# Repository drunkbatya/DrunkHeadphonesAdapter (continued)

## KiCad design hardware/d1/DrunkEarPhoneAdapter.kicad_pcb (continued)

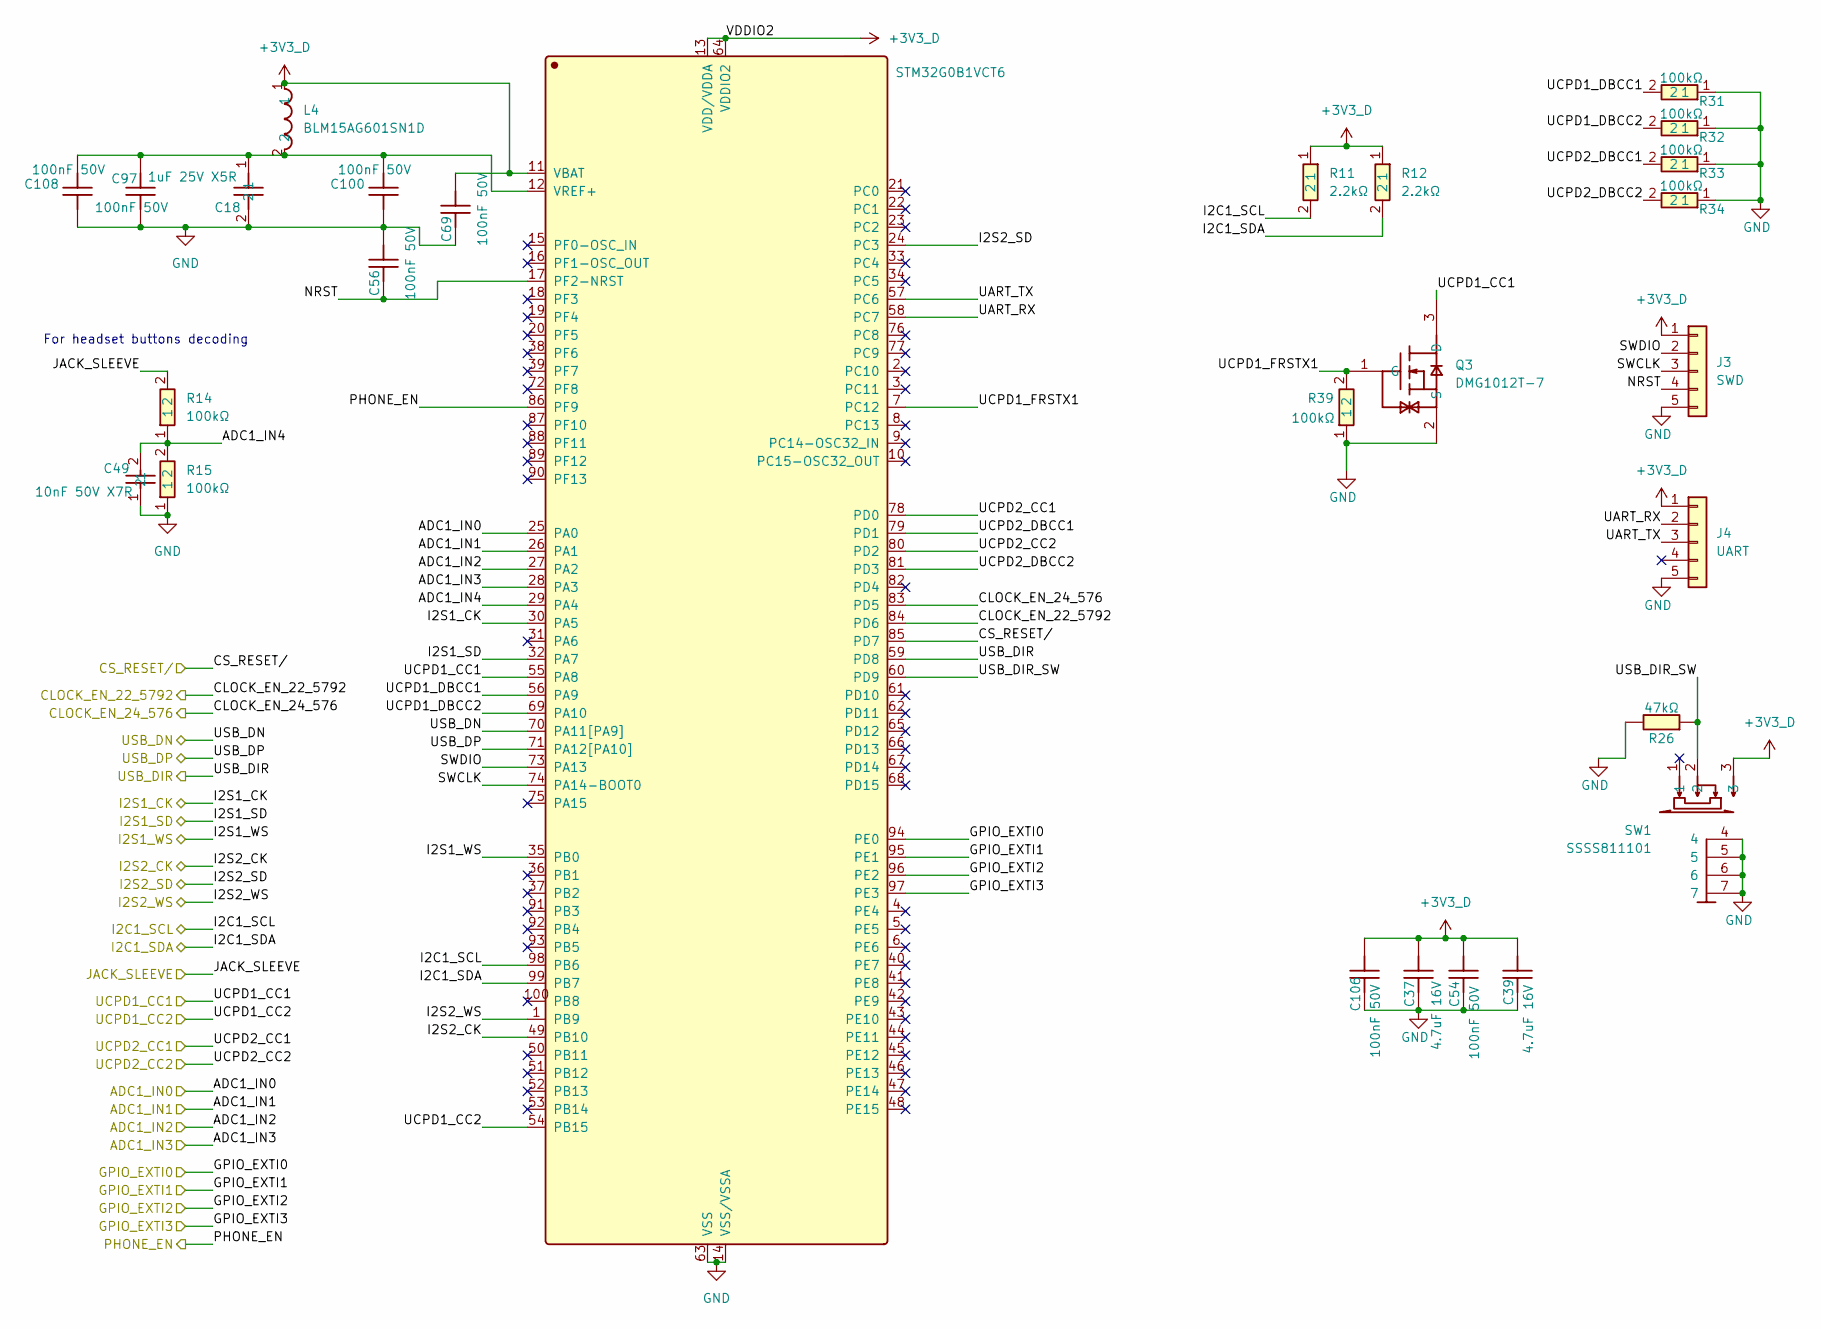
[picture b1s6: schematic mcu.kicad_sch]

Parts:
C18: 1uF 25V X5R; CL05A105KA5NQNC; Manufacturer Part CL05A105KA5NQNC; LCSC C52923
C37, C39: 4.7uF 16V; C_0603_1608Metric; Manufacturer Part CL10A475KO8NNNC; LCSC C19666
C49: 10nF 50V X7R; C_0402_1005Metric; Manufacturer Part CL05B103KB5NNNC; LCSC C15195
C54, C56, C69, C97, C100, C106, C108: 100nF 50V; C_0402_1005Metric; Manufacturer Part CL05B104KB54PNC; LCSC C307331
J3: SWD; Conn_1x5_1.27
J4: UART; Conn_1x5_1.27
L4: BLM15AG601SN1D; Manufacturer Part BLM15AG601SN1D; LCSC C76884
Q3: DMG1012T-7; SOT-523; Manufacturer Part DMG1012T-7; LCSC C20512
R11, R12: 2.2kΩ; R_0402_1005Metric; Manufacturer Part 0402WGF2201TCE; LCSC C25879
R14, R15, R31, R32, R33, R34, R39: 100kΩ; 0402WGF1003TCE; Manufacturer Part 0402WGF1003TCE; LCSC C25741
R26: 47kΩ; R_0402_1005Metric; Manufacturer Part 0402WGF4702TCE; LCSC C25792
SW1: SSSS811101; Manufacturer Part SSSS811101; LCSC C109335
U2: STM32G0B1VCT6; Manufacturer Part STM32G0B1VCT6; LCSC C3446137

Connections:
+3V3_D: C37.2, C39.2, C54.2, C69.2, C106.2, J3.1, J4.1, L4.1, R11.1, R12.1, SW1.3, U2.11 (VBAT), U2.13 (VDD/VDDA), U2.64 (VDDIO2); also elsewhere on the board
/adc/GMS1: R14.2; also elsewhere on the board
/adc/I2C_SCL: R11.2, U2.98 (PB6); also elsewhere on the board
/adc/I2C_SDA: R12.2, U2.99 (PB7); also elsewhere on the board
/adc/I2S_CK: U2.49 (PB10); also elsewhere on the board
/adc/I2S_SD: U2.24 (PC3); also elsewhere on the board
/adc/I2S_WS: U2.1 (PB9); also elsewhere on the board
/adc/INT/: U2.95 (PE1); also elsewhere on the board
/dac/CLOCK_EN_22_5792: U2.84 (PD6); also elsewhere on the board
/dac/CLOCK_EN_24_576: U2.83 (PD5); also elsewhere on the board
/dac/DAC_RESET/: U2.85 (PD7); also elsewhere on the board
/dac/I2S_CK: U2.30 (PA5); also elsewhere on the board
/dac/I2S_SD: U2.32 (PA7); also elsewhere on the board
/dac/I2S_WS: U2.35 (PB0); also elsewhere on the board
/dac//INT: U2.94 (PE0); also elsewhere on the board
/mcu/ADC1_IN0: U2.25 (PA0); also elsewhere on the board
/mcu/ADC1_IN1: U2.26 (PA1); also elsewhere on the board
/mcu/ADC1_IN2: U2.27 (PA2); also elsewhere on the board
/mcu/ADC1_IN3: U2.28 (PA3); also elsewhere on the board
/mcu/ADC1_IN4: C49.2, R14.1, R15.2, U2.29 (PA4)
/mcu/GPIO_EXTI2: U2.96 (PE2); also elsewhere on the board
/mcu/GPIO_EXTI3: U2.97 (PE3); also elsewhere on the board
/mcu/NRST: C56.1, J3.4, U2.17 (PF2-NRST)
/mcu/PHONE_EN: U2.86 (PF9); also elsewhere on the board
/mcu/SWCLK: J3.3, U2.74 (PA14-BOOT0)
/mcu/SWDIO: J3.2, U2.73 (PA13)
/mcu/UART_RX: J4.2, U2.58 (PC7)
/mcu/UART_TX: J4.3, U2.57 (PC6)
/mcu/UCPD1_CC1: Q3.3 (D), U2.55 (PA8); also elsewhere on the board
/mcu/UCPD1_CC2: U2.54 (PB15); also elsewhere on the board
/mcu/UCPD1_DBCC1: R31.2, U2.56 (PA9)
/mcu/UCPD1_DBCC2: R32.2, U2.69 (PA10)
/mcu/UCPD1_FRSTX1: Q3.1 (G), R39.2, U2.7 (PC12)
/mcu/UCPD2_CC1: U2.78 (PD0); also elsewhere on the board
/mcu/UCPD2_CC2: U2.80 (PD2); also elsewhere on the board
/mcu/UCPD2_DBCC1: R33.2, U2.79 (PD1)
/mcu/UCPD2_DBCC2: R34.2, U2.81 (PD3)
/mcu/USB_DIR: U2.59 (PD8); also elsewhere on the board
/mcu/USB_DIR_SW: R26.1, SW1.2, U2.60 (PD9)
/mcu/USB_DN: U2.70 (PA11[PA9]); also elsewhere on the board
/mcu/USB_DP: U2.71 (PA12[PA10]); also elsewhere on the board
GND: C18.2, C37.1, C39.1, C49.1, C54.1, C56.2, C69.1, C97.1, C100.1, C106.1, C108.1, J3.5, J4.5, Q3.2 (S), R15.1, R26.2, R31.1, R32.1, R33.1, R34.1, R39.1, SW1.4, SW1.5, SW1.6, SW1.7, U2.14 (VSS/VSSA), U2.63 (VSS); also elsewhere on the board
unnamed: C18.1, C97.2, C100.2, C108.2, L4.2, U2.12 (VREF+)

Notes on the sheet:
For headset buttons decoding

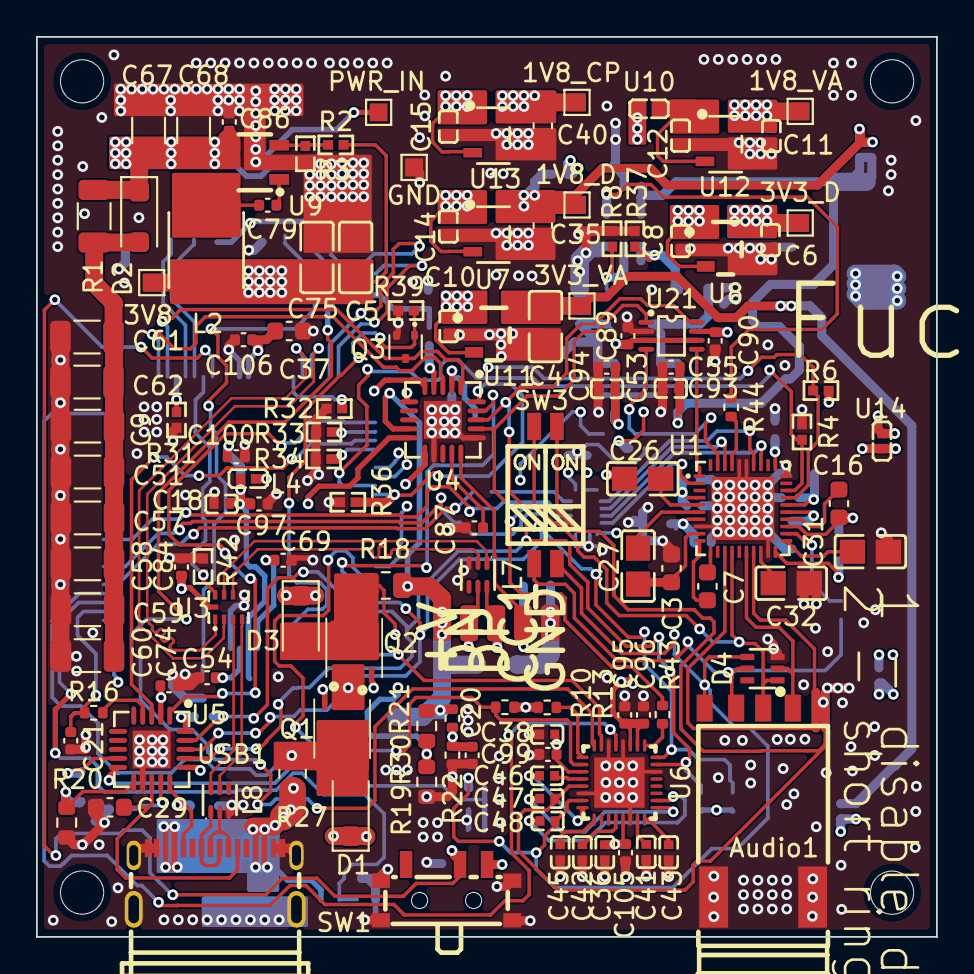
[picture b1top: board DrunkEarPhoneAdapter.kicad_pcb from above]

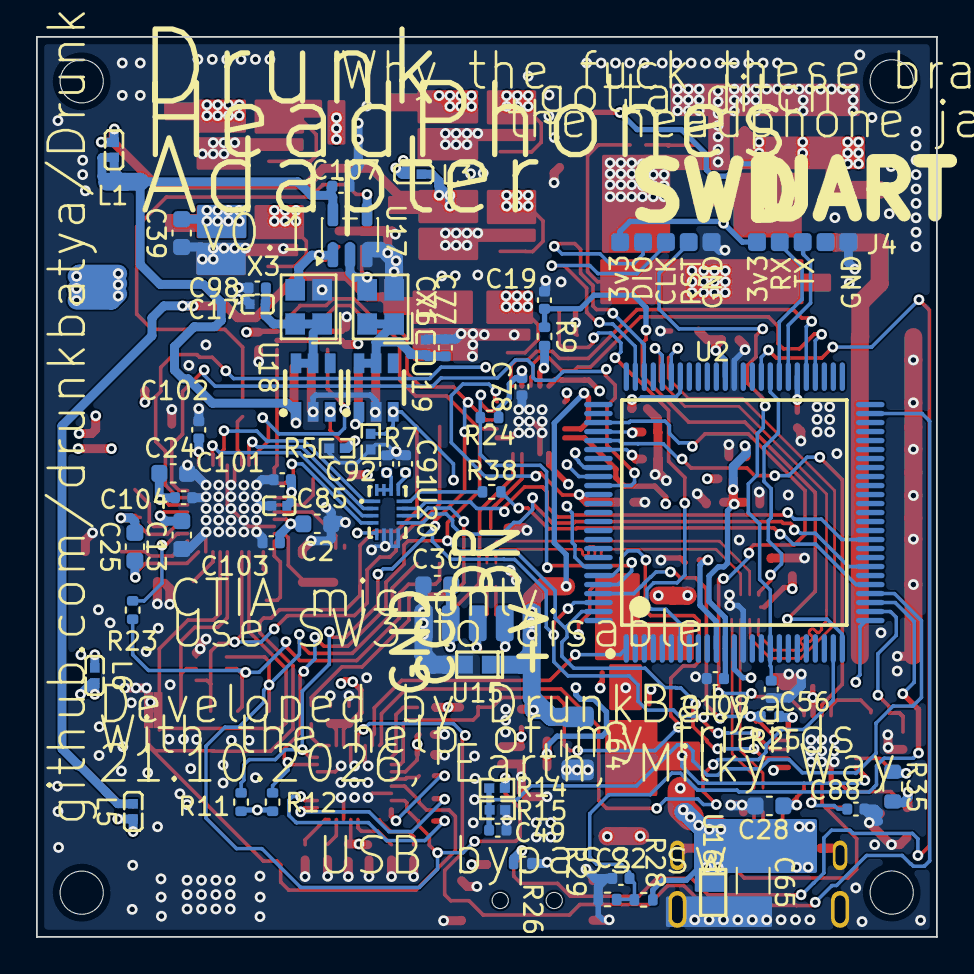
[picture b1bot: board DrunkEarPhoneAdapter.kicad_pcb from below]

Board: 4 copper layers, 50.0 x 50.0 mm, 188 parts (59 on the bottom side), 124 nets.

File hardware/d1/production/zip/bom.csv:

Designator,Footprint,Quantity,Value,LCSC Part #
AUDIO1,PJ-614,1,PJ-614,C145801
"C10, C11, C12, C14, C15, C17, C18, C36, C38, C41, C42, C43, C45, C46, C47, C48, C6, C76, C8, C85, C93, C94",CL05A105KA5NQNC,22,1uF 25V X5R,C52923
"C100, C101, C102, C103, C104, C105, C106, C107, C108, C53, C54, C55, C56, C69, C74, C77, C78, C79, C84, C86, C87, C88, C89, C90, C91, C92, C95, C96, C97, C98, C99",0402,31,100nF 50V,C307331
"C13, C16, C2, C25, C3, C7",0603,6,2.2uF 16V,C23630
"C19, C20, C21, C22",0402,4,1nF 50V,C1523
"C24, C35, C37, C39, C40",0603,5,4.7uF 16V,C19666
"C26, C27, C5, C75",CL21A226MAQNNNE,4,22uF 25V X5R,C45783
"C28, C29, C30",0603,3,330pF 50V,C1664
"C31, C32, C4",CC0805KKX7R9BB225,3,2.2uF 50V X7R,C125847
C49,0402,1,10nF 50V X7R,C15195
"C51, C57, C58, C59, C60, C61, C62, C9",1206,8,47uF 25V X5R,C76659
"C64, C65, C67, C68",1206,4,2.2uF 50V X7R,C50254
"D1, D2, D3",D_SOD-123F,3,PMEG4010CEH_115,C193342
D4,TPD4E1B06DCKR,1,TPD4E1B06DCKR,C840093
"L1, L3, L4, L5, L6",BLM15AG601SN1D,5,BLM15AG601SN1D,C76884
L2,SWPA4020S150MT,1,SWPA4020S150MT,C36407
"L7, L8",ECMF02-2AMX6,2,ECMF02-2AMX6,C2651144
"Q1, Q2",CSD17577Q3A,2,CSD17577Q3A,C201632
Q3,SOT-523,1,DMG1012T-7,C20512
R1,1206,1,100Ω 1206,C874066
"R10, R13, R22, R29",0402,4,10kΩ,C25744
"R11, R12",0402,2,2.2kΩ,C25879
"R14, R15, R31, R32, R33, R34, R36, R37, R39, R4, R42, R5, R6, R7, R8",0402WGF1003TCE,15,100kΩ,C25741
"R16, R23, R9",0402,3,1kΩ,C11702
R18,0805,1,10mΩ 500mW,C409060
"R19, R20",0603,2,549Ω,C23079
R2,0402WGF6202TCE,1,62kΩ,C37825
"R21, R28",0402,2,130kΩ,C93946
"R24, R25, R26",0402,3,47kΩ,C25792
R27,0805,1,7mΩ 500mW,C22450691
R3,0402WGF2202TCE,1,22kΩ,C25768
"R30, R35",0603,2,10kΩ,C25804
"R38, R43, R44",0402,3,33Ω,C25105
SW1,SSSS811101,1,SSSS811101,C109335
SW3,DSHP02TSGER,1,DSHP02TSGER,C3293142
TP1,TestPoint_Pad_1.0x1.0mm,1,3V3_D,
TP2,TestPoint_Pad_1.0x1.0mm,1,1V8_D,
TP3,TestPoint_Pad_1.0x1.0mm,1,1V8_CP,
TP4,TestPoint_Pad_1.0x1.0mm,1,1V8_VA,
TP5,TestPoint_Pad_1.0x1.0mm,1,3V3_VA,
TP6,TestPoint_Pad_1.0x1.0mm,1,3V8,
TP7,TestPoint_Pad_1.0x1.0mm,1,PWR_IN,
TP8,TestPoint_Pad_1.0x1.0mm,1,GND,
U1,CS43131-CNZR,1,CS43131-CNZR,C965907
"U10, U14",BLM15PX601SN1D,2,BLM15PX601SN1D,C160977
"U11, U8",TPS7A2033PDBVR,2,TPS7A2033PDBVR,C2862740
"U12, U13, U7",TPS7A2018PDBVR,3,TPS7A2018PDBVR,C963430
"U15, U16",ESDA25P35-1U1M_C19829649,2,ESDA25P35-1U1M,C19829649
U17,SOT-23-5,1,SN74LVC1G32DBVR,C10096
"U18, U19",TPS22917DBVR,2,TPS22917DBVR,C2681320
U2,STM32G0B1VCT6,1,STM32G0B1VCT6,C3446137
U20,SN74AVC4T774RSVR,1,SN74AVC4T774RSVR,C779392
U21,TCA9406DCUR,1,TCA9406DCUR,C840107
U3,TS3USB221RSER,1,TS3USB221RSER,C130085
"U4, U5",TCPP03-M20,2,TCPP03-M20,C3662955
U6,ES8327,1,ES8327,C5145122
U9,TPS560430XFDBVR,1,TPS560430XFDBVR,C523980
USB1,2130830005,1,2130830005,C2839029
X1,SX2M22_5792M20F30TNN,1,22.5792MHz,C5452663
X3,SX2M22_5792M20F30TNN,1,24.576MHz,C5452664

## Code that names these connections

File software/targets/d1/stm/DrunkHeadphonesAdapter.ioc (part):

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Mcu.Name=STM32G0B1V(B-C-E)Tx
Mcu.Package=LQFP100
Mcu.UserName=STM32G0B1VCTx
PA0.Mode=IN0
PA0.Signal=ADC1_IN0
PA1.Mode=IN1
PA1.Signal=ADC1_IN1
PA11\ [PA9].Mode=Device
PA11\ [PA9].Signal=USB_DM
PA12\ [PA10].Mode=Device
PA12\ [PA10].Signal=USB_DP
PA13.Mode=Serial_Wire
PA13.Signal=SYS_SWDIO
PA14-BOOT0.Mode=Serial_Wire
PA14-BOOT0.Signal=SYS_SWCLK
PA2.Mode=IN2
PA2.Signal=ADC1_IN2
PA3.Mode=IN3
PA3.Signal=ADC1_IN3
PA4.Mode=IN4
PA4.Signal=ADC1_IN4
PA5.Mode=Half_Duplex_Slave
PA5.Signal=I2S1_CK
PA7.Mode=Half_Duplex_Slave
PA7.Signal=I2S1_SD
PA8.Mode=Dual_Role_AllSignals
PA8.Signal=UCPD1_CC1
PB0.Mode=Half_Duplex_Slave
PB0.Signal=I2S1_WS
PB10.Mode=Half_Duplex_Slave
PB10.Signal=I2S2_CK
PB12.Mode=FRSTX_CC2
PB12.Signal=UCPD2_FRSTX1
PB14.Mode=FRSTX_CC2
PB14.Signal=UCPD1_FRSTX2
PB15.Mode=Dual_Role_AllSignals
PB15.Signal=UCPD1_CC2
PB6.Mode=I2C
PB6.Signal=I2C1_SCL
PB7.Mode=I2C
PB7.Signal=I2C1_SDA
PB9.Mode=Half_Duplex_Slave
PB9.Signal=I2S2_WS
PC12.Mode=FRSTX_CC2
PC12.Signal=UCPD1_FRSTX1
PC3.Mode=Half_Duplex_Slave
PC3.Signal=I2S2_SD
PC6.Mode=Asynchronous
PC6.Signal=LPUART2_TX
PC7.Mode=Asynchronous
PC7.Signal=LPUART2_RX
PC8.Mode=FRSTX_CC2
PC8.Signal=UCPD2_FRSTX2
PD0.Mode=Dual_Role_AllSignals
PD0.Signal=UCPD2_CC1
PD2.Mode=Dual_Role_AllSignals
PD2.Signal=UCPD2_CC2
PD5.GPIOParameters=GPIO_Label
PD5.GPIO_Label=CLK_EN1
PD5.Signal=GPIO_Output
PD6.GPIOParameters=GPIO_Label
PD6.GPIO_Label=CLK_EN2
PD6.Signal=GPIO_Output
PD7.GPIOParameters=GPIO_Label
PD7.GPIO_Label=CS_RESET/
PD7.Signal=GPIO_Output
PD8.GPIOParameters=GPIO_Label
PD8.GPIO_Label=USB_DIR
PD8.Signal=GPIO_Output
PD9.GPIOParameters=GPIO_Label
PD9.GPIO_Label=USB_DIR_SW
PD9.Signal=GPIO_Input
PE0.GPIOParameters=GPIO_ModeDefaultEXTI
PE0.GPIO_ModeDefaultEXTI=GPIO_MODE_IT_FALLING
PE0.Signal=GPXTI0
PE1.GPIOParameters=GPIO_ModeDefaultEXTI
PE1.GPIO_ModeDefaultEXTI=GPIO_MODE_IT_FALLING
PE1.Signal=GPXTI1
PE2.GPIOParameters=GPIO_ModeDefaultEXTI
PE2.GPIO_ModeDefaultEXTI=GPIO_MODE_IT_FALLING
PE2.Signal=GPXTI2
PE3.GPIOParameters=GPIO_ModeDefaultEXTI
PE3.GPIO_ModeDefaultEXTI=GPIO_MODE_IT_FALLING
PE3.Signal=GPXTI3
PF9.GPIOParameters=GPIO_Label
PF9.GPIO_Label=PHONE_EN
PF9.Signal=GPIO_Output
RCC.HSE_VALUE=16000000
RCC.SYSCLKFreq_VALUE=64000000
RCC.SYSCLKSource=RCC_SYSCLKSOURCE_PLLCLK
board=custom
